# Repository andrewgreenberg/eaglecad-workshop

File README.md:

# Andrew's EAGLE CAD Workshop

You really want to hear me rant for 3 hours straight? OK, I warned you ;) These workshops are intensive 3 hour courses designed to get you going on making circuit boards.

## Getting Ready

- Homework for class
   - Please follow "File Setup" part of the [Setup instructions](https://github.com/andrewgreenberg/eaglecad-workshop/blob/master/EAGLE-CAD-Setup.md). You can do the rest, but we'll do them in the workshop, too.
- Equipment for class
   - A laptop with EAGLE (see homework above) and probably a mouse.

## Workshop overview

- Schematics!
   - What are schematics
   - Schematics that don't suck
   - Making schematics in EAGLE
   - Schematic Checklist
- PCB layout!
   - What are PCBs
   - Layouts that don't suck
   - Laying out boards in EAGLE
   - Layout Checklist

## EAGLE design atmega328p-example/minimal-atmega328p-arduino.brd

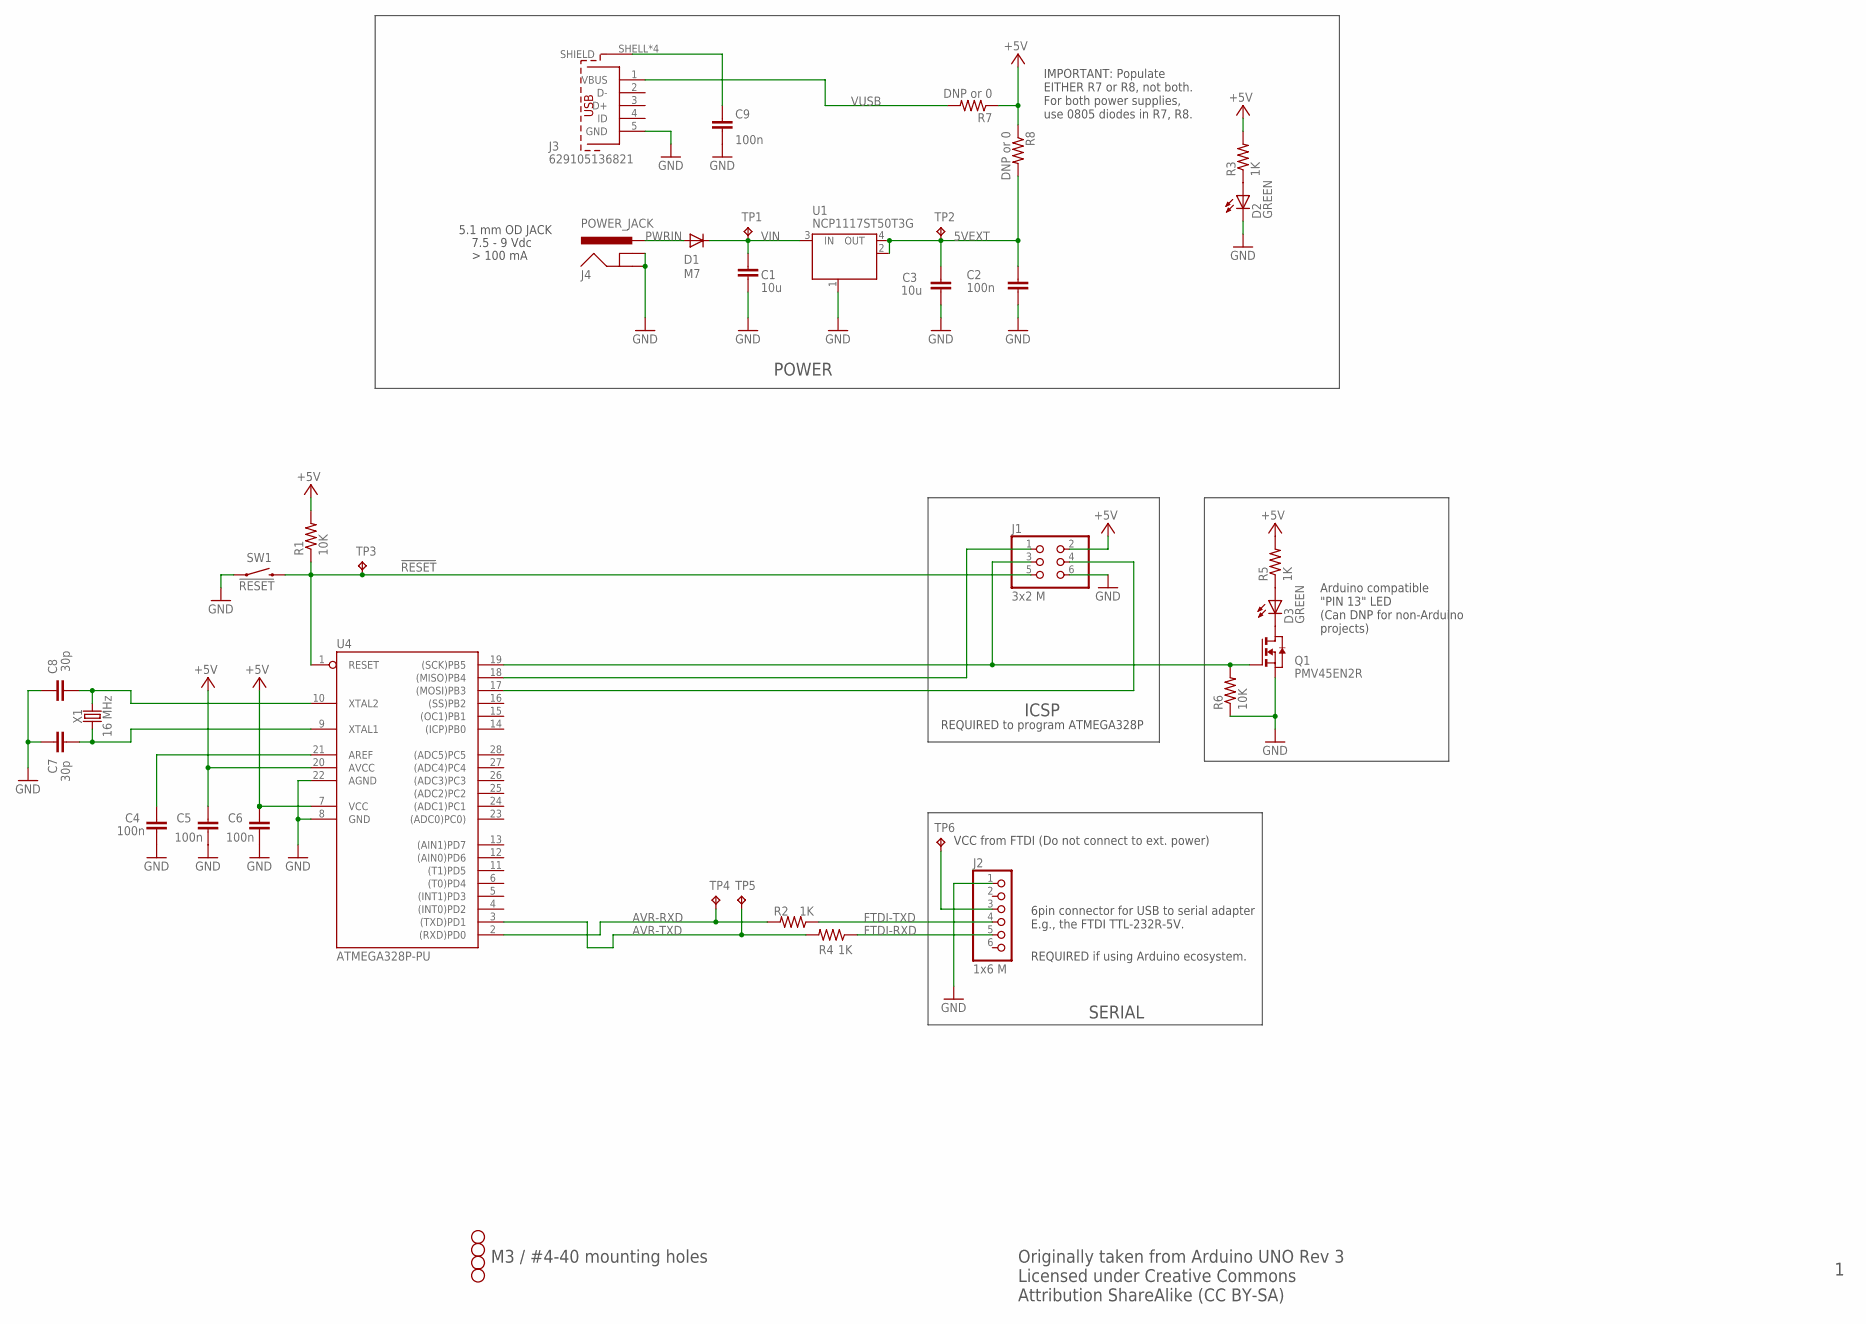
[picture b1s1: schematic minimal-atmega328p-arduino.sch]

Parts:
C1, C3: 10u; C0805K; MPN CL21A106KOQNNNG
C2, C4, C5, C6, C9: 100n; C0805K; MPN CL21B104KBCNNNC
C7: 30p; C0805K; MPN CL21C180JBANNNC
C8: 30p; C0805K; MPN CL21C300JBANNNC
D1: M7; SMB; MPN 10BQ030TR
D2, D3: GREEN; CHIP-LED0805; MPN 150080GS75000
H1, H2, H3, H4: STAND-OFF
J1: 3x2 M; 2X03; MPN M20-9980345
J2: 1x6 M; 1X06; MPN PRPC006SAAN-RC
J3: 629105136821; MPN 629105136821
J4: POWER_JACK; POWER_JACK_PTH; MPN PJ-202A
Q1: PMV45EN2R; SOT-23; MPN PMV45EN2R
R1, R6: 10K; R0805; MPN RC0805FR-0710KL
R2, R3, R4, R5: 1K; R0805; MPN RC0805FR-071KL
R7, R8: DNP or 0; R0805; MPN RC0805JR-070RL
SW1: !RESET; TACTILE_SWITCH_SMD; MPN RS-187R05A2-DS MT RT
TP1, TP2, TP3, TP4, TP5, TP6: TPPAD1-13; P1-13
U1: NCP1117ST50T3G; SOT223; MPN NCP1117ST50T3G
U4: ATMEGA328P-PU; DIL28-3; MPN ATMEGA328P-PU
X1: 16 MHz; HC49UP; MPN ECS-160-18-5PX-TR

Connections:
5VEXT: C2.2, C3.1, R8.2, TP2.TP, U1.2 (OUT), U1.4 (OUT)
!RESET: J1.5, R1.1, SW1.3 (2), TP3.TP, U4.1 (RESET)
+5V: C5.2, C6.2, J1.2, R1.2, R3.2, R5.2, R7.1, R8.1, U4.7 (VCC), U4.20 (AVCC)
AVR-RXD: R2.2, TP4.TP, U4.2 ((RXD)PD0)
AVR-TXD: R4.2, TP5.TP, U4.3 ((TXD)PD1)
FTDI-RXD: J2.5, R4.1
FTDI-TXD: J2.4, R2.1
GND: C1.2, C2.1, C3.2, C4.1, C5.1, C6.1, C7.2, C8.2, C9.1, D2.C, J1.6, J2.1, J3.5 (GND), J4.GND, J4.GNDBREAK, Q1.2 (S), R6.1, SW1.1, U1.1 (GND/ADJ), U4.8 (GND), U4.22 (AGND)
MISO: J1.1, U4.18 ((MISO)PB4)
MOSI: J1.4, U4.17 ((MOSI)PB3)
unnamed: C4.2, U4.21 (AREF)
unnamed: D3.A, R5.1
unnamed: D2.A, R3.1
unnamed: D3.C, Q1.1 (D)
unnamed: J2.3, TP6.TP
unnamed: C9.2, J3.SHELL (SHIELD), J3.SHELL1 (SHIELD), J3.SHELL2 (SHIELD), J3.SHELL3 (SHIELD)
PWRIN: D1.A, J4.PWR
SCK: J1.3, Q1.3 (G), R6.2, U4.19 ((SCK)PB5)
VIN: C1.1, D1.C, TP1.TP, U1.3 (IN)
VUSB: J3.1 (VBUS), R7.2
XTAL1: C7.1, U4.9 (XTAL1), X1.1
XTAL2: C8.1, U4.10 (XTAL2), X1.2

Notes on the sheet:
7.5 - 9 Vdc
POWER
ICSP
5.1 mm OD JACK
6pin connector for USB to serial adapter E.g., the FTDI TTL-232R-5V.
REQUIRED if using Arduino ecosystem.
M3 / #4-40 mounting holes
SERIAL
REQUIRED to program ATMEGA328P
Arduino compatible "PIN 13" LED (Can DNP for non-Arduino projects)
VCC from FTDI (Do not connect to ext. power)
IMPORTANT: Populate EITHER R7 or R8, not both. For both power supplies, use 0805 diodes in R7, R8.
Originally taken from Arduino UNO Rev 3 Licensed under Creative Commons Attribution ShareAlike (CC BY-SA)

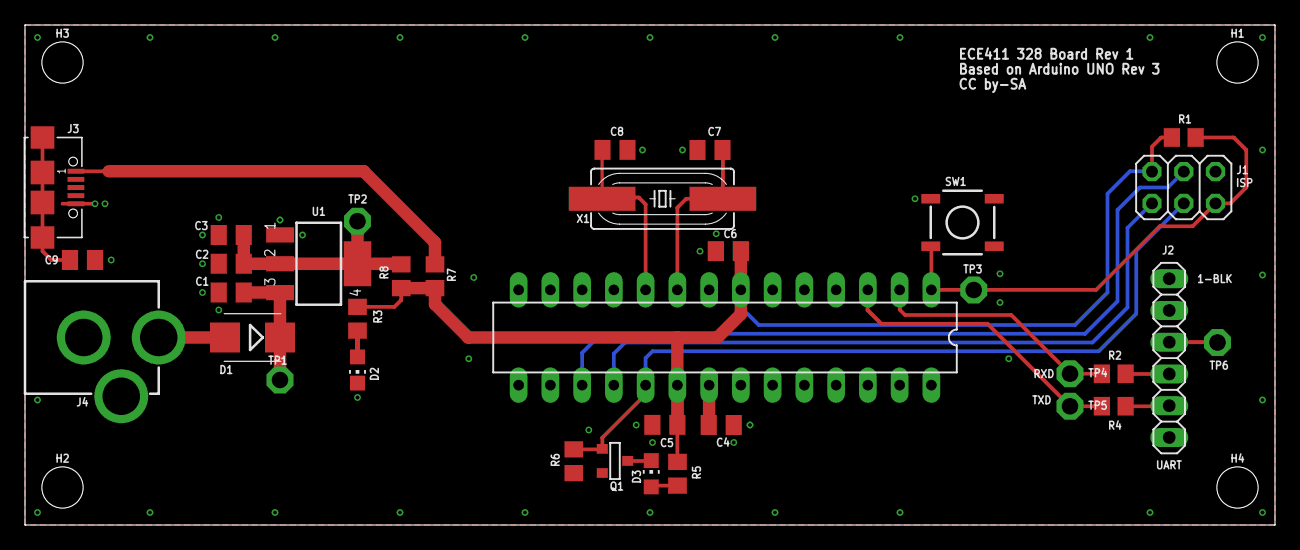
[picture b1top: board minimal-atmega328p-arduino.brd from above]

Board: 2 copper layers, 100.0 x 40.0 mm, 39 parts (0 on the bottom side), 22 nets.

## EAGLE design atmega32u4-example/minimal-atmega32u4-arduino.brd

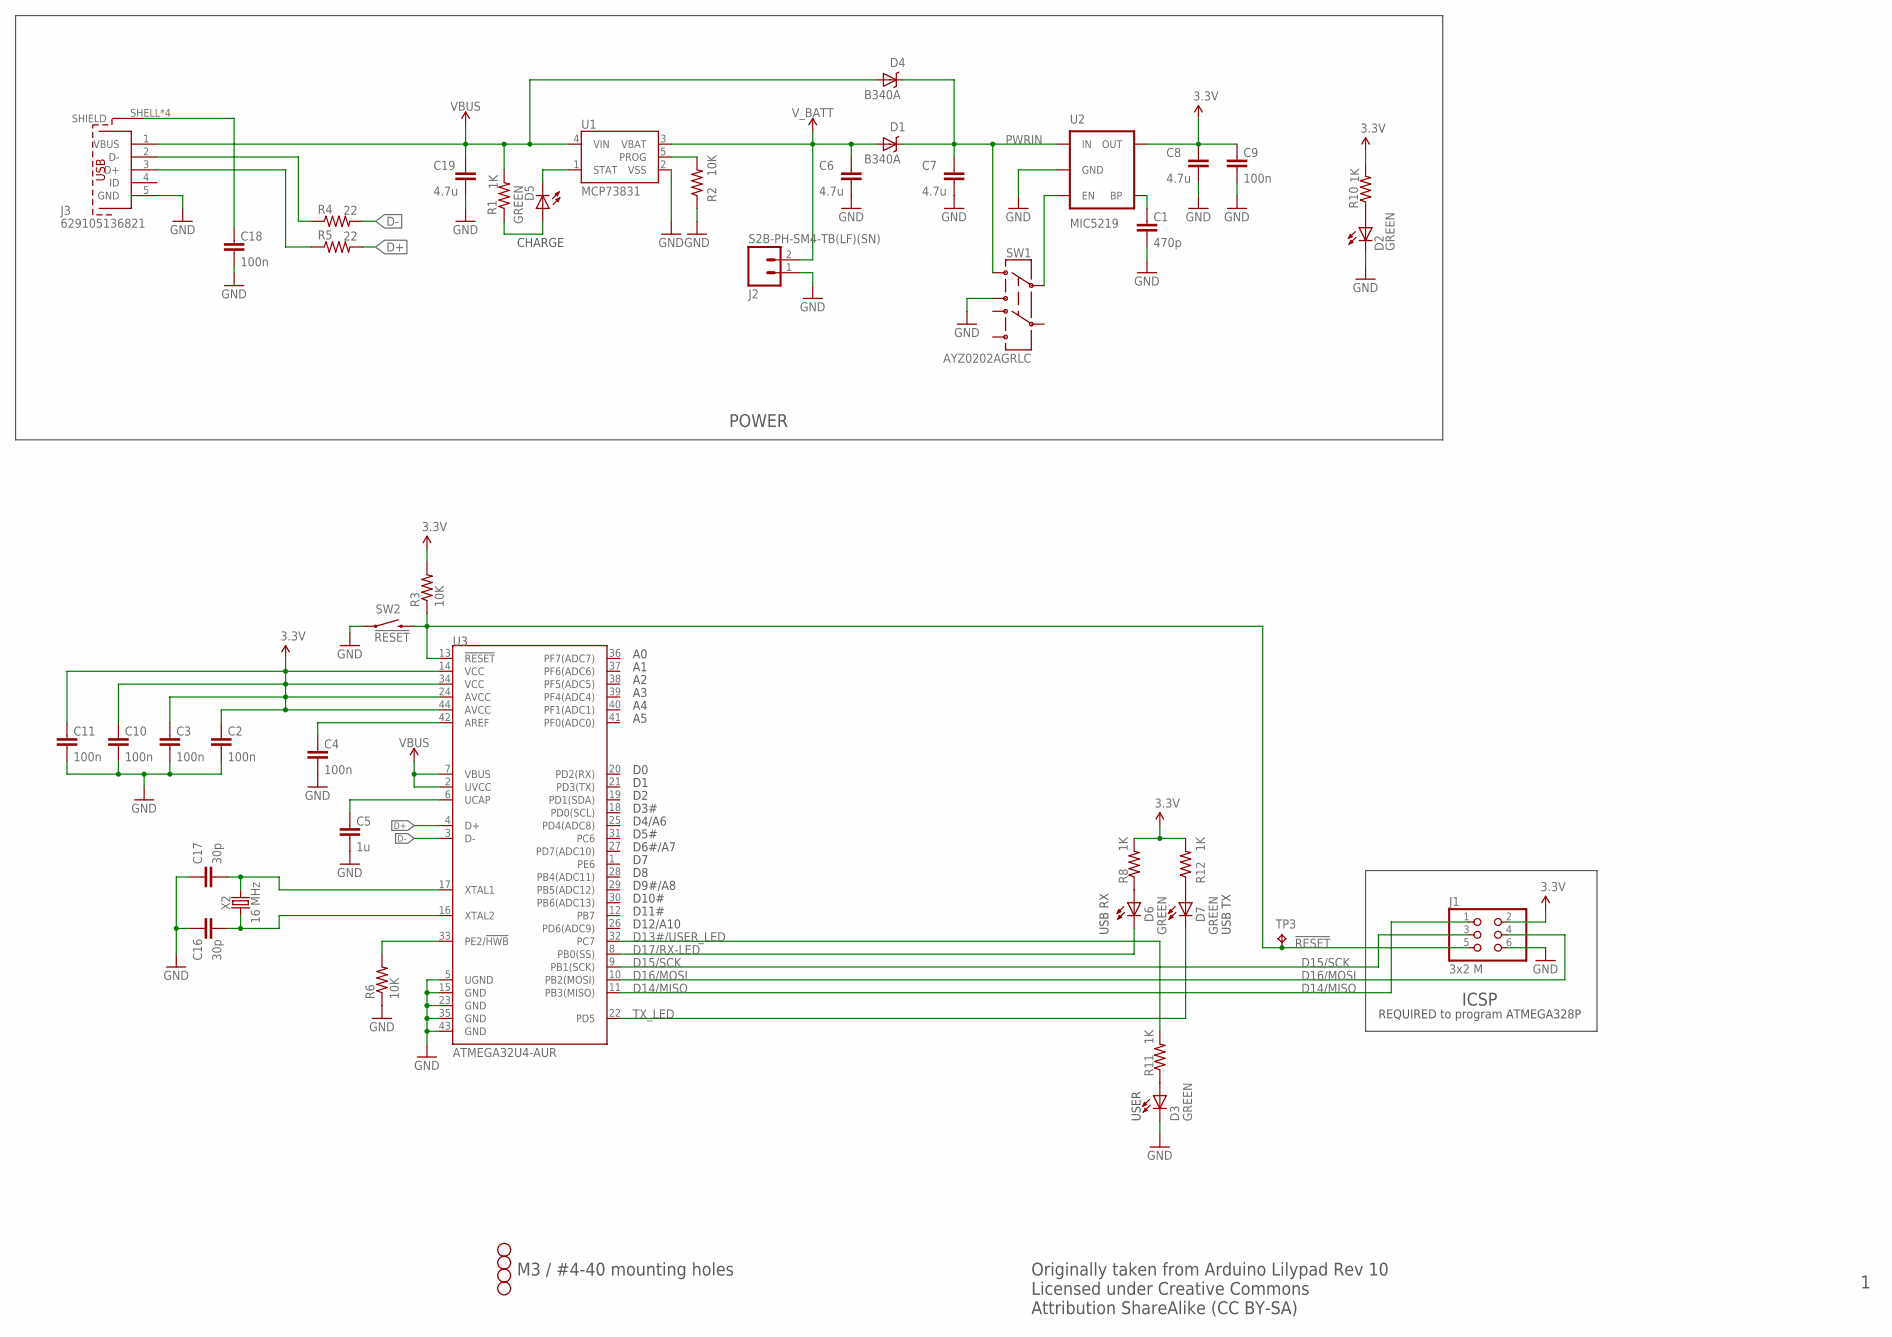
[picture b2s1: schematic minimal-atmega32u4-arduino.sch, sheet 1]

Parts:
C1: 470p; C0805K; MPN CL21B471KBANNNC
C2, C3, C4, C9, C10, C11, C18: 100n; C0805K; MPN CL21B104KBCNNNC
C5: 1u; C0805K; MPN CL21B105KOFNNNG
C6, C7, C8, C19: 4.7u; C0805K; MPN CL21A475KOFNNNE
C16: 30p; C0805K; MPN CL21C300JBANNNC
C17: 30p; C0805K; MPN CL21C180JBANNNC
D1, D4: B340A; SMA-DIODE; MPN B340AE-13
D2, D3, D5, D6, D7: GREEN; CHIP-LED0805; MPN 150080GS75000
H1, H2, H3, H4: STAND-OFF
J1: 3x2 M; 2X03; MPN M20-9980345
J2: S2B-PH-SM4-TB(LF)(SN); JST-2-SMD; MPN S2B-PH-SM4-TB(LF)(SN)
J3: 629105136821; MPN 629105136821
R1, R8, R10, R11, R12: 1K; R0805; MPN RC0805FR-071KL
R2, R3, R6: 10K; R0805; MPN RC0805FR-0710KL
R4, R5: 22; R0805; MPN RC0805FR-0722RL
SW1: AYZ0202AGRLC; AYZ0202; MPN AYZ0202AGRLC
SW2: !RESET; TACTILE_SWITCH_SMD; MPN RS-187R05A2-DS MT RT
TP3: TPPAD1-13; P1-13
U1: MCP73831; SOT23-5; MPN MCP73831T-2ACI/OT
U2: MIC5219; SOT23-5; MPN MIC5219-3.3YM5-TR
U3: ATMEGA32U4-AUR; TQFP44; MPN ATMEGA32U4-AUR
X2: 16 MHz; HC49UP; MPN ECS-160-18-5PX-TR

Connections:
3.3V: C2.1, C3.1, C8.1, C9.1, C10.1, C11.1, J1.2, R3.2, R8.2, R10.2, R12.2, U2.5 (OUT), U3.14 (VCC), U3.24 (AVCC), U3.34 (VCC), U3.44 (AVCC)
!RESET: J1.5, R3.1, SW2.3 (2), TP3.TP, U3.13 (!RESET)
AREF: C4.1, U3.42 (AREF)
D13#/USER_LED: R11.2, U3.32 (PC7)
D14/MISO: J1.1, U3.11 (PB3(MISO))
D15/SCK: J1.3, U3.9 (PB1(SCK))
D16/MOSI: J1.4, U3.10 (PB2(MOSI))
D17/RX-LED: D6.C, U3.8 (PB0(SS))
D+: R5.2, U3.4 (D+)
D-: R4.2, U3.3 (D-)
GND: C1.2, C2.2, C3.2, C4.2, C5.2, C6.2, C7.2, C8.2, C9.2, C10.2, C11.2, C16.2, C17.2, C18.2, C19.2, D2.C, D3.C, J1.6, J2.1 (2), J3.5 (GND), R2.1, R6.1, SW1.3, SW2.1, U1.2 (VSS), U2.2 (GND), U3.5 (UGND), U3.15 (GND), U3.23 (GND), U3.35 (GND), U3.43 (GND)
MCPPROG: R2.2, U1.5 (PROG)
MIC-BP: C1.1, U2.4 (BP)
MIC-EN: SW1.2, U2.3 (EN)
unnamed: D5.A, R1.1
unnamed: D5.C, U1.1 (STAT)
unnamed: D2.A, R10.1
unnamed: D3.A, R11.1
unnamed: C18.1, J3.SHELL (SHIELD), J3.SHELL1 (SHIELD), J3.SHELL2 (SHIELD), J3.SHELL3 (SHIELD)
unnamed: D6.A, R8.1
unnamed: D7.A, R12.1
unnamed: J3.2 (D-), R4.1
unnamed: J3.3 (D+), R5.1
PE2/!HWB: R6.2, U3.33 (PE2/!HWB)
PWRIN: C7.1, D1.C, D4.C, SW1.1, U2.1 (IN)
TX_LED: D7.C, U3.22 (PD5)
UCAP: C5.1, U3.6 (UCAP)
VBUS: C19.1, D4.A, J3.1 (VBUS), R1.2, U1.4 (VIN), U3.2 (UVCC), U3.7 (VBUS)
V_BATT: C6.1, D1.A, J2.2 (1), U1.3 (VBAT)
XTAL1: C17.1, U3.17 (XTAL1), X2.2
XTAL2: C16.1, U3.16 (XTAL2), X2.1

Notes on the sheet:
CHARGE
Originally taken from Arduino Lilypad Rev 10 Licensed under Creative Commons Attribution ShareAlike (CC BY-SA)
POWER
M3 / #4-40 mounting holes
ICSP
REQUIRED to program ATMEGA328P
USB RX
USB TX
USER
D3#
D4/A6
D5#
D6#/A7
D9#/A8
D10#
D11#
D12/A10

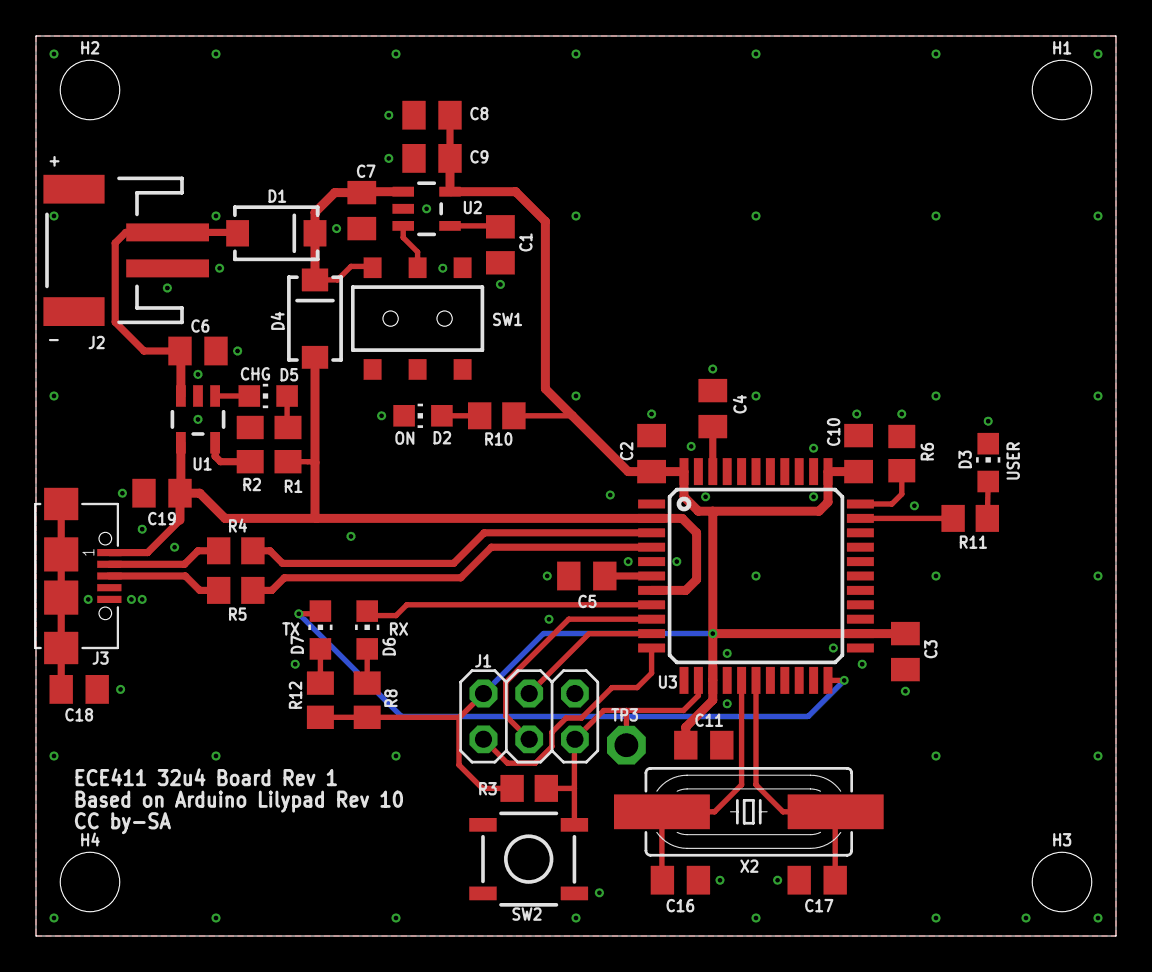
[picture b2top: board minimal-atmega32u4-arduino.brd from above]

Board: 2 copper layers, 60.0 x 50.0 mm, 46 parts (0 on the bottom side), 31 nets.

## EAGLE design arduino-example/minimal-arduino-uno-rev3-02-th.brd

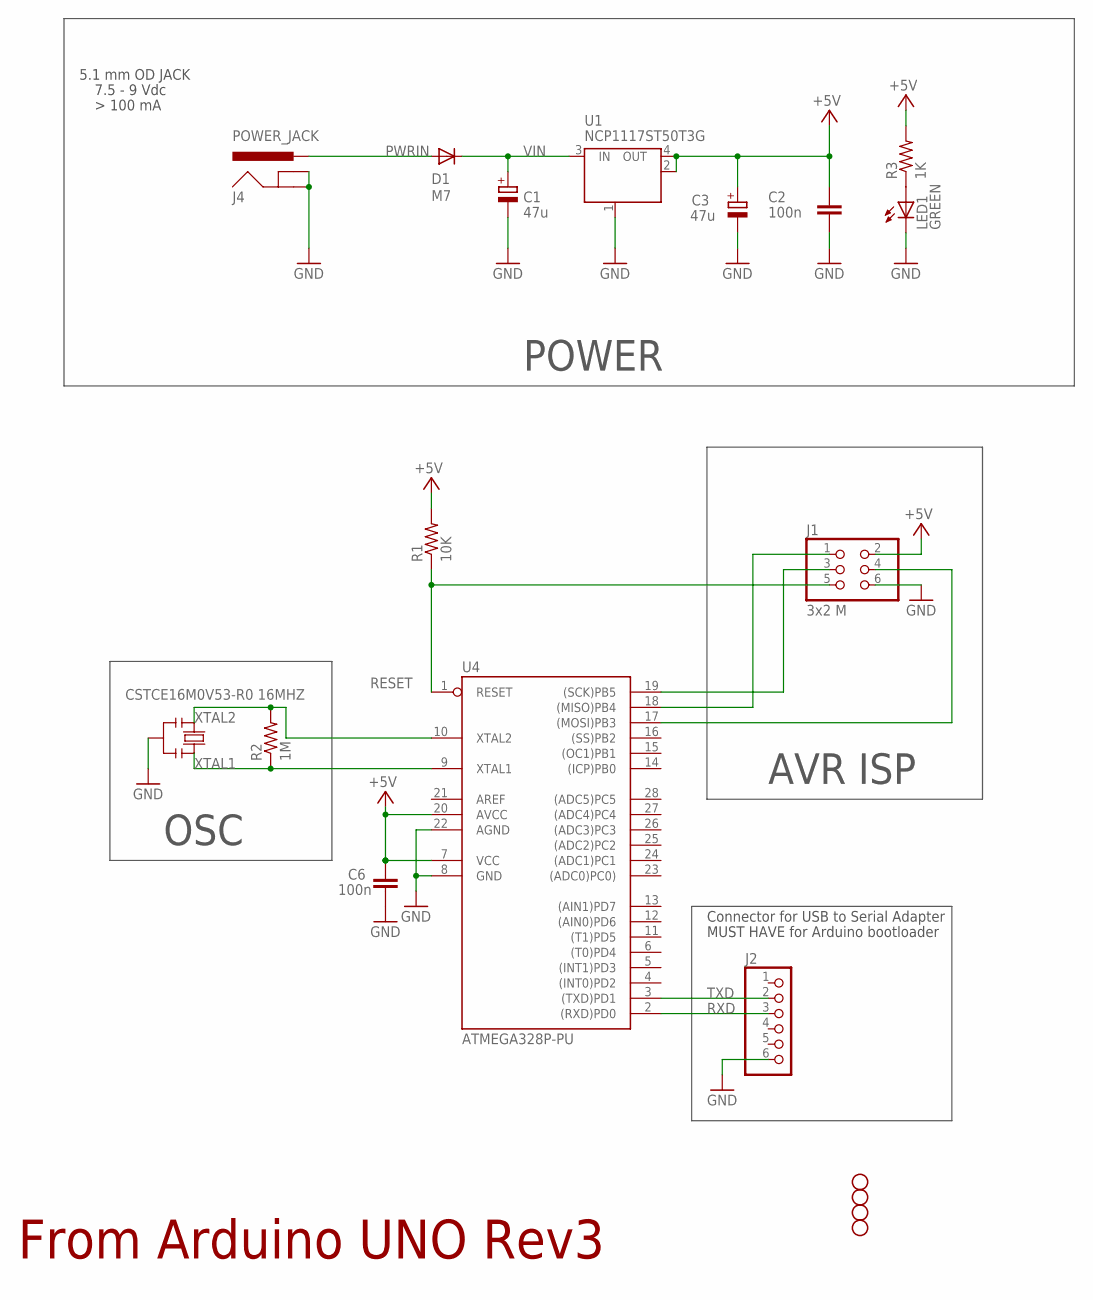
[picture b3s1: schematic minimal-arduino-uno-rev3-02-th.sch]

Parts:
C1, C3: 47u; PANASONIC_D
C2, C6: 100n; C0805
D1: M7; SMB
H1, H2, H3, H4: STAND-OFF
J1: 3x2 M; 2X03
J2: PINHD-1X6; 1X06
J4: POWER_JACK; POWER_JACK_PTH
LED1: GREEN; CHIP-LED0805
R1: 10K; R0805
R2: 1M; R0805
R3: 1K; R0805
U1: NCP1117ST50T3G; SOT223
U4: ATMEGA328P-PU; DIL28-3
X1: CSTCE16M0V53-R0 16MHZ; RESONATOR

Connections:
+5V: C2.2, C3.+, C6.2, J1.2, R1.2, R3.2, U1.2 (OUT), U1.4 (OUT), U4.7 (VCC), U4.20 (AVCC)
GND: C1.-, C2.1, C3.-, C6.1, J1.6, J2.6, J4.GND, J4.GNDBREAK, LED1.C, U1.1 (GND/ADJ), U4.8 (GND), U4.22 (AGND), X1.2
MISO: J1.1, U4.18 ((MISO)PB4)
MOSI: J1.4, U4.17 ((MOSI)PB3)
unnamed: LED1.A, R3.1
PWRIN: D1.A, J4.PWR
RESET: J1.5, R1.1, U4.1 (RESET)
RXD: J2.3, U4.2 ((RXD)PD0)
SCK: J1.3, U4.19 ((SCK)PB5)
TXD: J2.2, U4.3 ((TXD)PD1)
VIN: C1.+, D1.C, U1.3 (IN)
XTAL1: R2.1, U4.9 (XTAL1), X1.3
XTAL2: R2.2, U4.10 (XTAL2), X1.1

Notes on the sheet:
From Arduino UNO Rev3
7.5 - 9 Vdc
POWER
AVR ISP
OSC
5.1 mm OD JACK
Connector for USB to Serial Adapter
MUST HAVE for Arduino bootloader

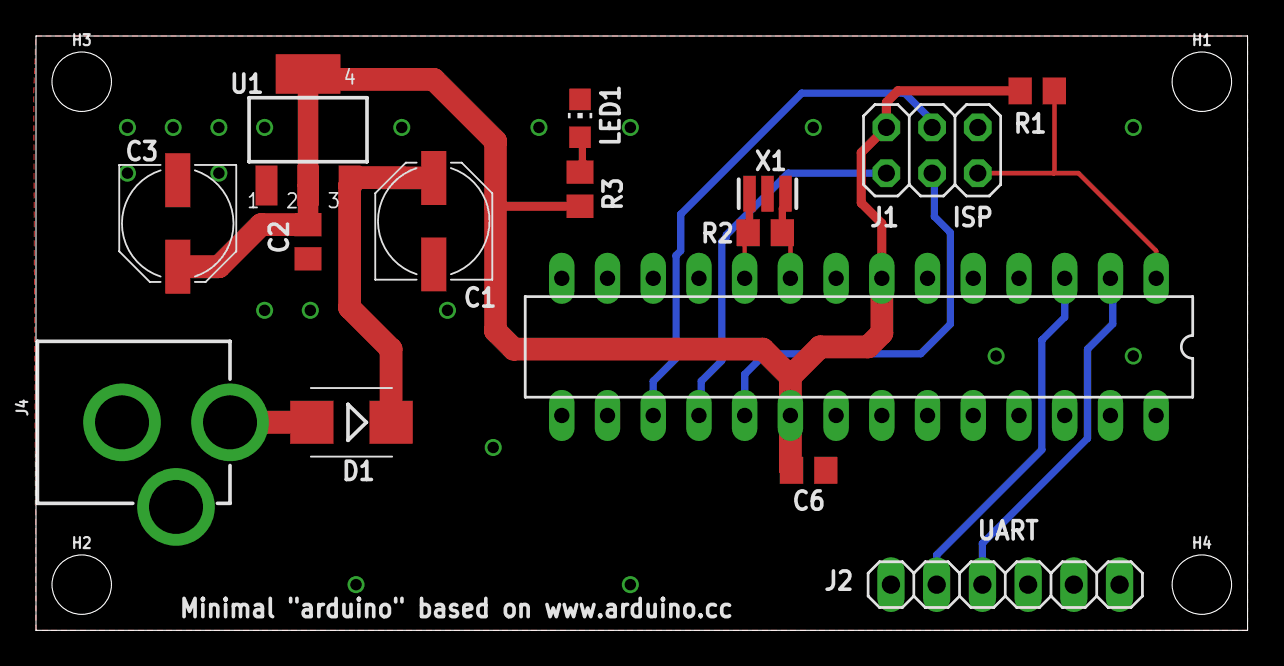
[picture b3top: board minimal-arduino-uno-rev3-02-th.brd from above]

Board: 2 copper layers, 67.3 x 33.0 mm, 19 parts (0 on the bottom side), 13 nets.

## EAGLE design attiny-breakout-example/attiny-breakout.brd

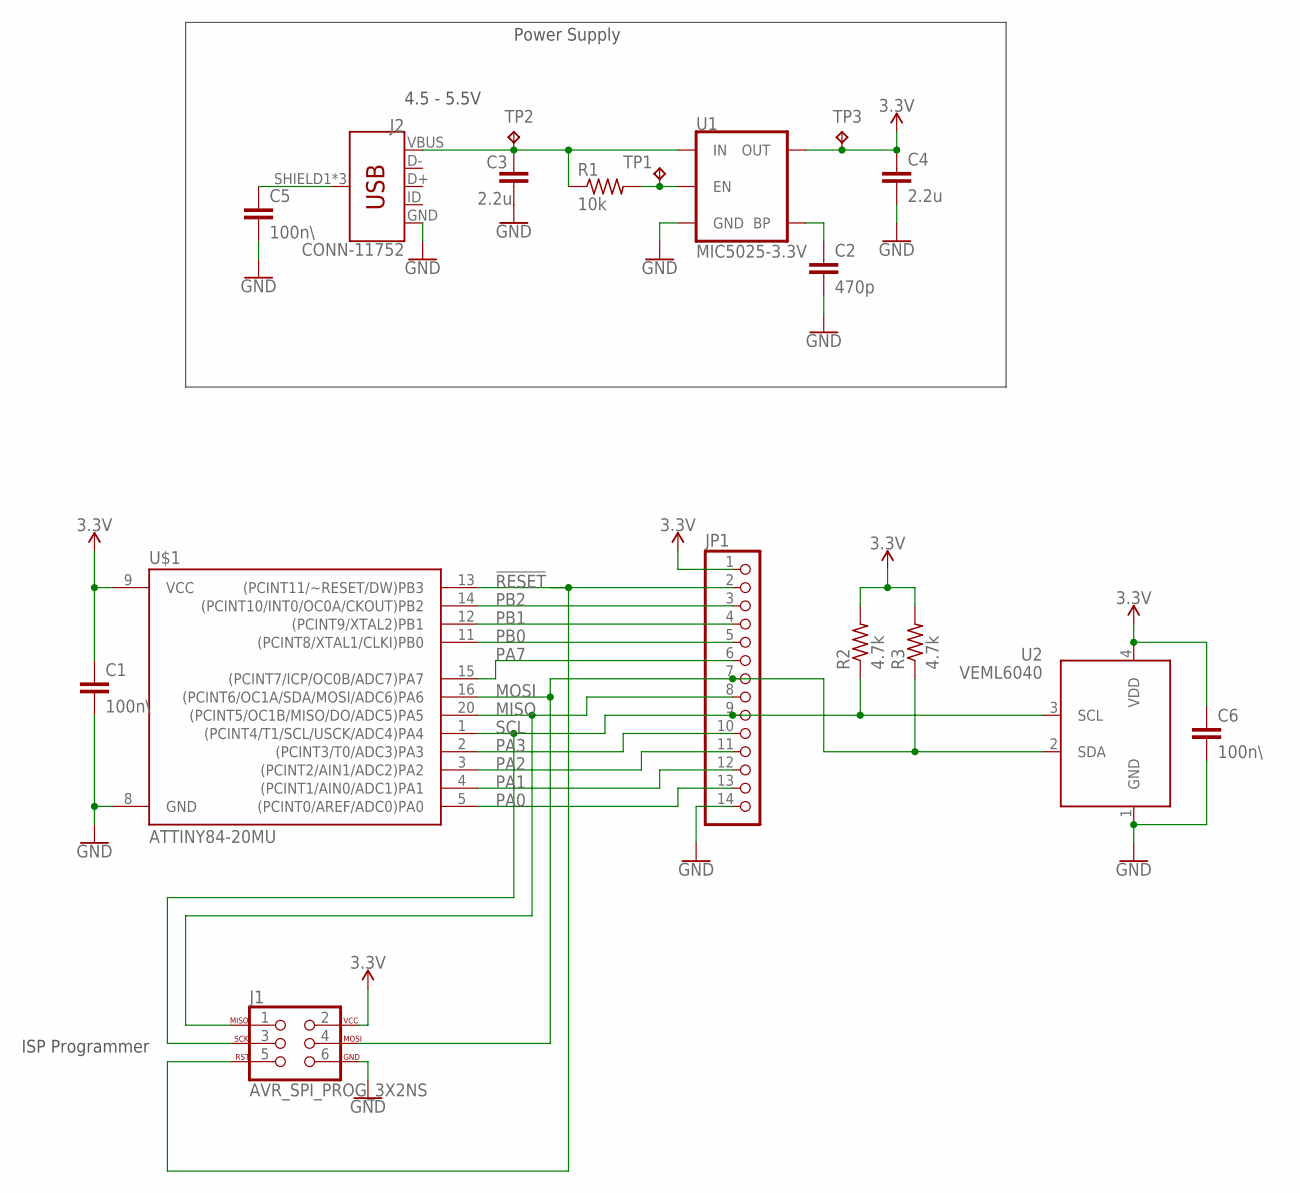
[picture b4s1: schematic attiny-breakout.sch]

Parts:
C1, C5, C6: 100n\; C0805
C2: 470p; C0805
C3, C4: 2.2u; C0805
J1: AVR_SPI_PROG_3X2NS; 2X3-NS
J2: CONN-11752; USB-B-MICRO-SMD
JP1: PINHD-1X14; 1X14
R1: 10k; R0805
R2, R3: 4.7k; R0805
TP1, TP2, TP3: TPPAD1-13; P1-13
U1: MIC5025-3.3V; SOT23-5
U2: VEML6040
U$1: ATTINY84-20MU; QFN20

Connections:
3.3V: C1.1, C4.1, C6.1, J1.2, JP1.1, R2.2, R3.2, TP3.TP, U1.5 (OUT), U2.4 (VDD), U$1.9 (VCC)
!RESET: J1.5, JP1.2, U$1.13 ((PCINT11/~RESET/DW)PB3)
BP: C2.1, U1.4 (BP)
EN: R1.2, TP1.TP, U1.3 (EN)
GND: C1.2, C2.2, C3.2, C4.2, C5.2, C6.2, J1.6, J2.GND, JP1.14, U1.2 (GND), U2.1 (GND), U$1.8 (GND)
MISO: J1.1, JP1.8, U$1.20 ((PCINT5/OC1B/MISO/DO/ADC5)PA5)
MOSI: J1.4, JP1.7, R3.1, U2.2 (SDA), U$1.16 ((PCINT6/OC1A/SDA/MOSI/ADC6)PA6)
unnamed: C5.1, J2.SHIELD1 (SHIELD), J2.SHIELD2 (SHIELD), J2.SHIELD3 (SHIELD)
PA0: JP1.13, U$1.5 ((PCINT0/AREF/ADC0)PA0)
PA1: JP1.12, U$1.4 ((PCINT1/AIN0/ADC1)PA1)
PA2: JP1.11, U$1.3 ((PCINT2/AIN1/ADC2)PA2)
PA3: JP1.10, U$1.2 ((PCINT3/T0/ADC3)PA3)
PA7: JP1.6, U$1.15 ((PCINT7/ICP/OC0B/ADC7)PA7)
PB0: JP1.5, U$1.11 ((PCINT8/XTAL1/CLKI)PB0)
PB1: JP1.4, U$1.12 ((PCINT9/XTAL2)PB1)
PB2: JP1.3, U$1.14 ((PCINT10/INT0/OC0A/CKOUT)PB2)
SCL: J1.3, JP1.9, R2.1, U2.3 (SCL), U$1.1 ((PCINT4/T1/SCL/USCK/ADC4)PA4)
VBUS: C3.1, J2.VBUS, R1.1, TP2.TP, U1.1 (IN)

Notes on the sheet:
Power Supply
4.5 - 5.5V
ISP Programmer

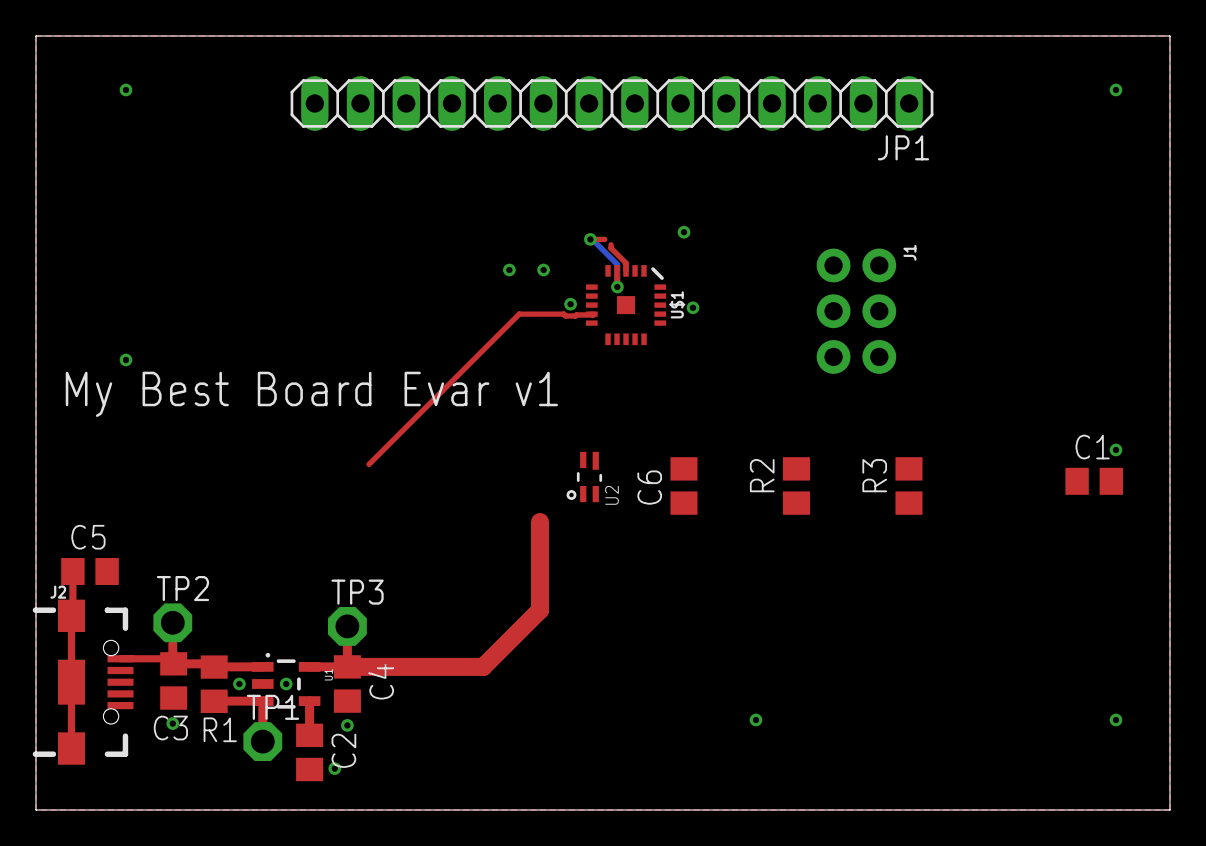
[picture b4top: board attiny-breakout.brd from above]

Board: 2 copper layers, 63.0 x 43.0 mm, 18 parts (0 on the bottom side), 18 nets.

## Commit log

2016-11-02 eagle key bindings
2017-10-14 Broke up into modular files.
2017-10-14 Ooooo better. Notes, DRC file.
2017-10-14 Better organization, and committed workshop EAGLE files.
2017-10-15 Latest bits of the attiny breakout board, and the color sensors library.
2017-10-15 Updated readme based on class today.
2017-10-19 Fixed typos
2018-01-27 Not sure why this isn't committed, so here you go.
2018-01-27 Latest OSH Park design rules.
2018-01-27 Bettererer documentaiton, breaking up by step.
2018-01-27 added checklits and example files.
2018-10-27 Removed old file
2018-10-27 Organization
2018-11-01 Updated minimal arduino board.
2019-01-19 Updated to EAGLE 9.
2019-02-10 Added eagle command line thing for Linux.
2019-10-24 Initial save of atmega32u4 project, and updated scripts for 9.5.1
2019-10-27 Updated ATMEGA328P schematic and layout to modernish standards. Still needs attributes and BOM.
2019-10-27 Finished ATMega328P example board.
2019-10-27 Removed vestigial classes.
2019-10-27 Added microusb connector for power with DNP zero ohms, updated BOM.
2019-10-28 Added reset switch, moved programming wires to bottom layer.
2019-10-28 Removed stupid layers.
2019-10-28 Finished layout and BOM of ATMEGA32u4 board. Uses mostly the same parts as the 328 board now.
2019-10-28 Updated for EAGLE 9.5.1
2019-10-29 Eeek! Bad cap values for the crystal oscillator. Changed from 18pF to 30 pF based on 18 pF load cap and 0805 capacitors.
2020-01-18 Better setup instructions.
2020-01-18 Updated README.
2020-01-18 updated checklists.

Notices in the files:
parts and their libraries:
SparkFun-Connectors: Licensing: Creative Commons ShareAlike 4.0 International - https://creativecommons.org/licenses/by-sa/4.0
Wurth_Elektronik_Electromechanic_Input-O: Copyright: Würth Elektronik
